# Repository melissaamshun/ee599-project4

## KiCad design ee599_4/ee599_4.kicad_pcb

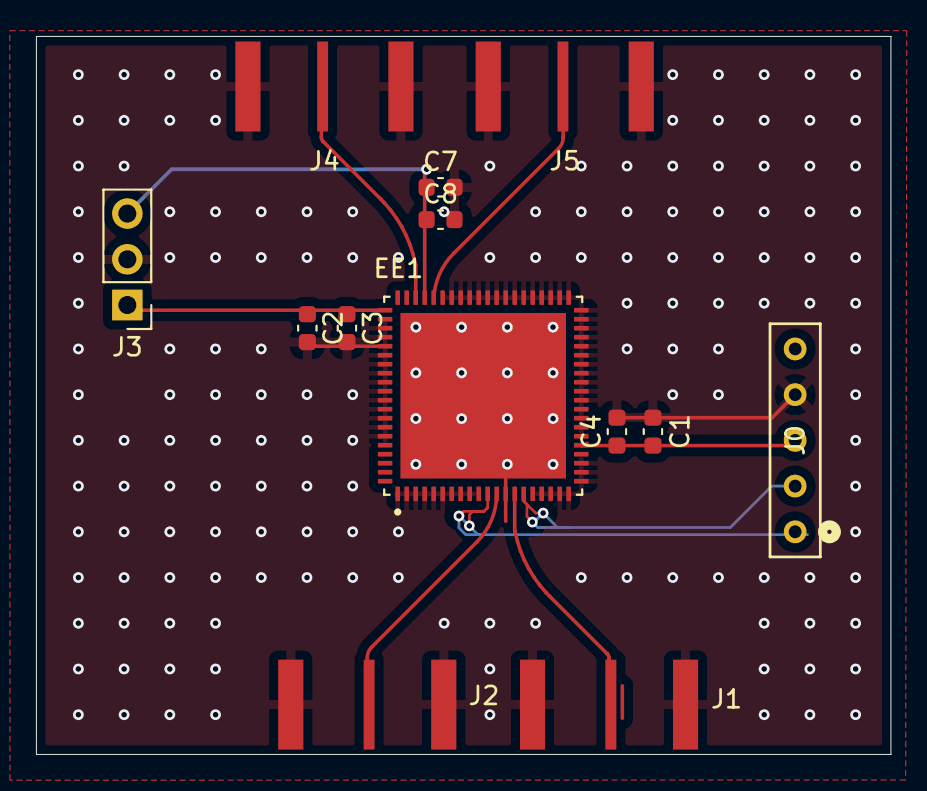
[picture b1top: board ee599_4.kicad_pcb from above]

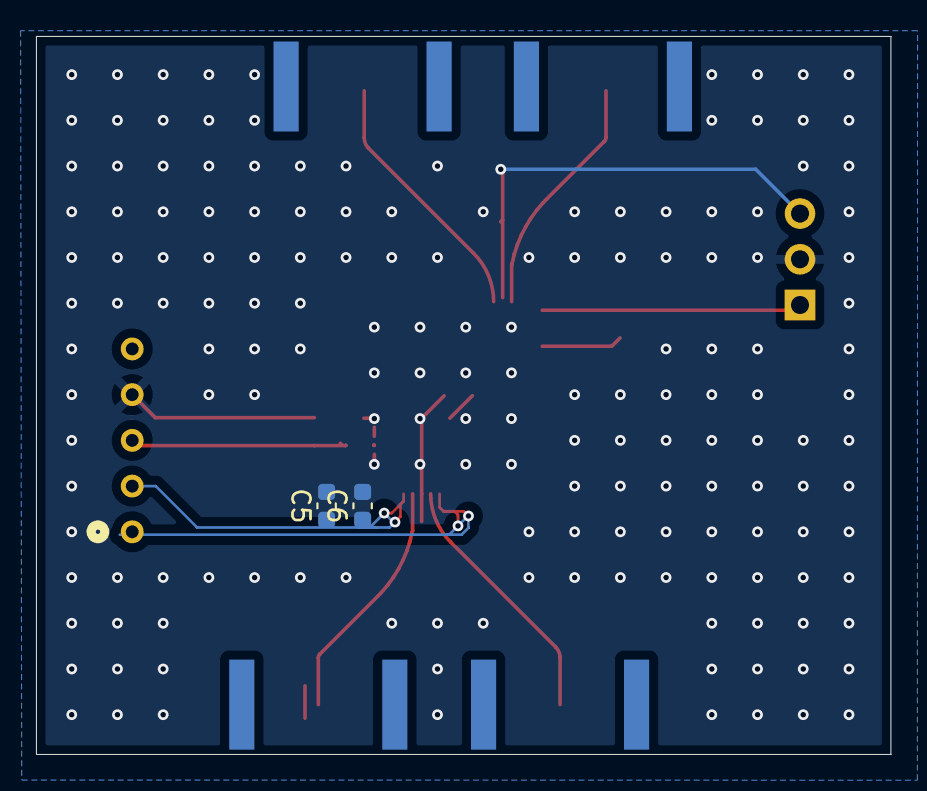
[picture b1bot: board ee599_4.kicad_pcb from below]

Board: 4 copper layers, 47.5 x 39.9 mm, 15 parts (2 on the bottom side), 10 nets.

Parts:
C1, C2, C5, C7: 10uF; C_0603_1608Metric
C3, C4, C6, C8: 100pF; C_0603_1608Metric
EE1: QFN50P1100X1100X90-81N
J0: TS-105-G-A; CON5_1X5_TU_HTS_SAI
J1, J2, J4, J5: 60312202114512
J3: Conn_01x03_Pin; PinHeader_1x03_P2.54mm_Vertical

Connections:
F0_Mel: EE1.12 (F0_Mel), J2.1
GND: C1.2, C2.2, C3.2, C4.2, C5.2, C6.2, C7.2, C8.2, EE1.1 (Vdd_TIFet), EE1.2 (Out_TIFet), EE1.3 (VC_Kai), EE1.4 (VS_Kai), EE1.5 (VC_Jae), EE1.6 (VSS_Jae), EE1.7 (Voutp_Jae), EE1.8 (VDD_Sim), EE1.9 (VC_Sim), EE1.10 (VSS_Sim), EE1.13 (GND_Mel), EE1.16 (Amp_Out+), EE1.17 (AMP_IN-), EE1.18 (AMP_IN+), EE1.19 (AMP_Out-), EE1.20 (VC_Hay), EE1.21 (NC), EE1.22 (NC), EE1.23 (NC), EE1.24 (VS_Hay), EE1.26 (GND_Hay), EE1.27 (A1_Hay), EE1.28 (A2_Hay), EE1.29 (A3_Hay), EE1.30 (AMP_CLK00), EE1.31 (T2_Jam), EE1.32 (T1_Jam), EE1.33 (VS_Jam), EE1.34 (VSS_Bar), EE1.35 (VDD_Bar), EE1.36 (VC_Jam), EE1.37 (VC_Hua), EE1.38 (NC), EE1.39 (NC), EE1.40 (IN_TiFet), EE1.41 (A1_Bar), EE1.42 (B2_Bar), EE1.43 (B0_Bar), EE1.44 (VS_Bar), EE1.45 (VC_Bar), EE1.46 (A0_Bar), EE1.47 (B1_Bar), EE1.48 (B1_Sim), EE1.49 (B2_Sim), EE1.50 (A2_Sim), EE1.51 (A1_Sim), EE1.52 (VS_Sim), EE1.53 (VS_Jae), EE1.54 (VDD_Jae), EE1.55 (Voutp2_Jae), EE1.62 (NC), EE1.63 (NC), EE1.64 (VS_Hay), EE1.65 (VSS_Min), EE1.66 (Out_Hua), EE1.67 (VS_Hua), EE1.68 (VSS_Kai), EE1.69 (TN2_Kai), EE1.70 (TN1_Kai), EE1.71 (TP3_Kai), EE1.72 (TP2_Kai), EE1.73 (TP1_Kai), EE1.74 (VDD_Kai/Hua), EE1.75 (VSS_TiFet), EE1.76 (Out_Hua), J0.4, J1.2, J2.2, J3.2, J4.2, J5.2
VC_Mel: C5.1, C6.1, EE1.15 (VC_Mel), J0.2
VC_Min: C7.1, C8.1, EE1.57 (VC_Min), J3.3
VDD_Mel: C1.1, C4.1, EE1.25 (VDD_Mel), J0.3
VDD_Min: C2.1, C3.1, EE1.61 (VDD_Min), J3.1
VS_Mel: EE1.11 (VS_Mel), J0.1
f180_Mel: EE1.14 (f180_Mel), J1.1
fVCO_0_Min: EE1.58 (fVCO_0_Min), J4.1
fVCO_180_Min: EE1.56 (fVCO_180_Min), J5.1

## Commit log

2025-04-08 hate github
2025-04-08 schematic updated
2025-04-15 started minjings, still need to work on it
2025-04-16 minjing osc layout
